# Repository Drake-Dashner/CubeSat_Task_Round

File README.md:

# CubeSat_Task_Round
Contain my Task 3 for CubeSat Task round 1

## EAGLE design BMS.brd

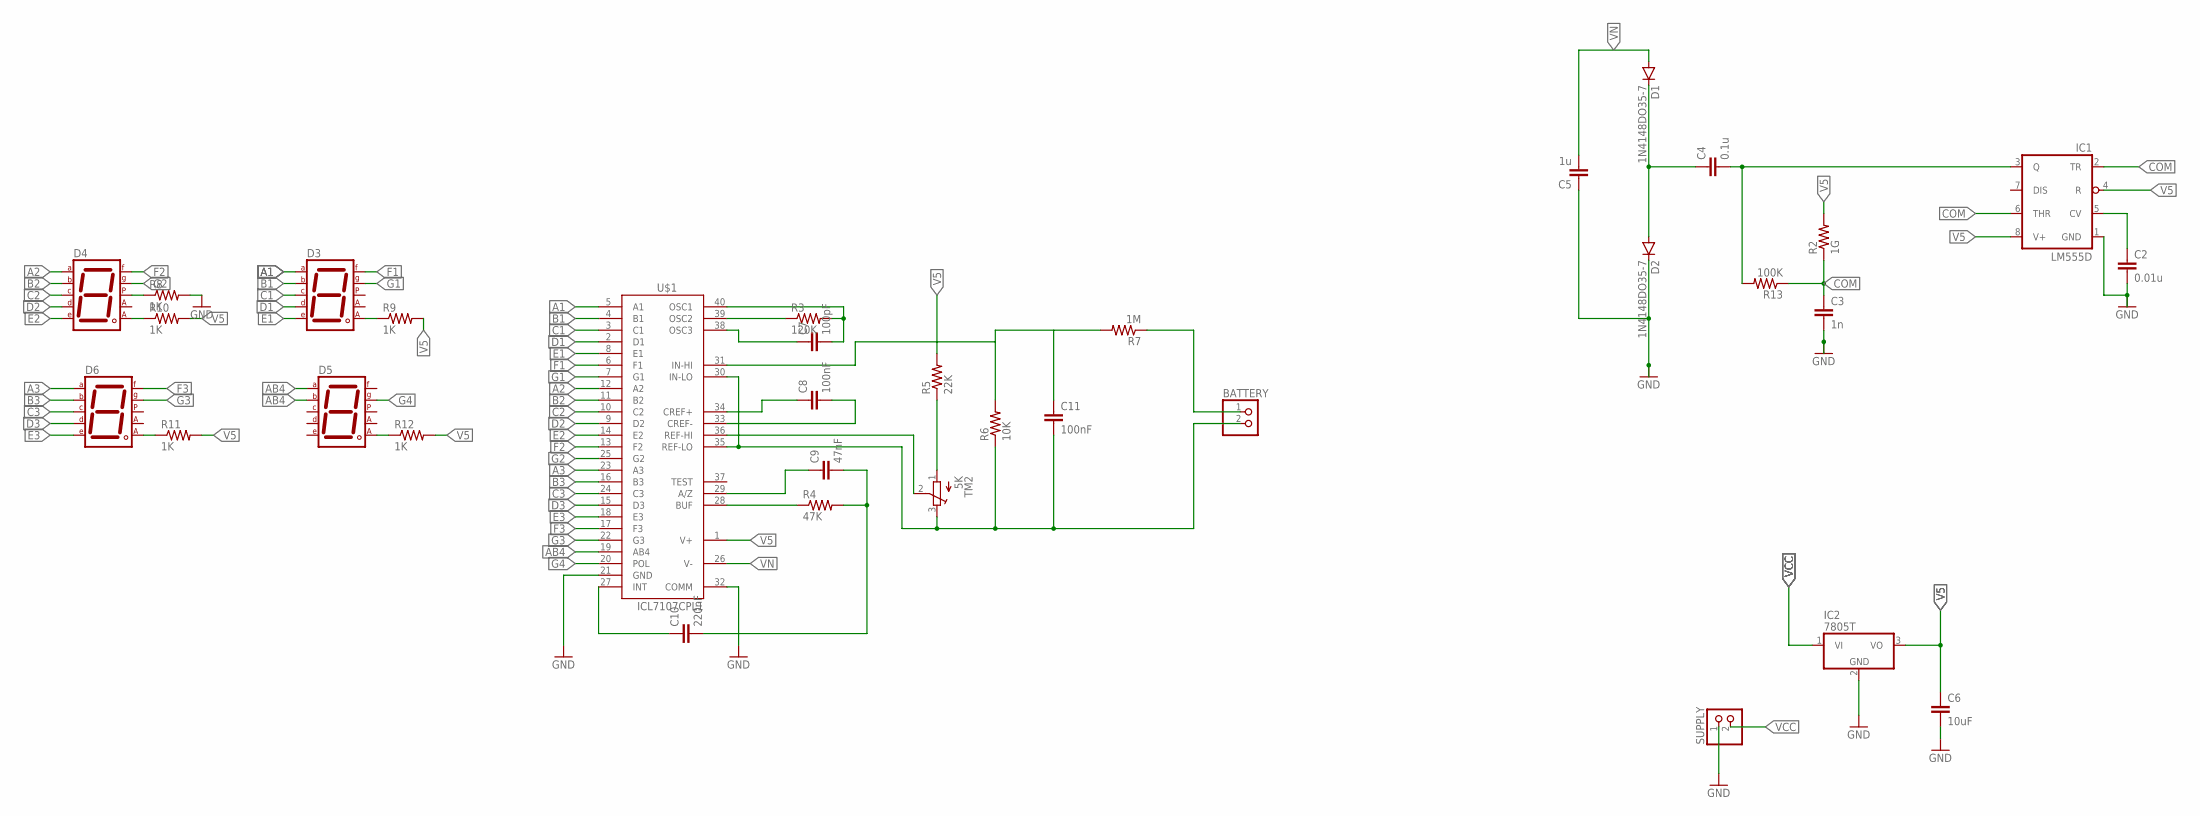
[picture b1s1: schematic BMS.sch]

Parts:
BATTERY: PINHD-1X2; 1X02
C2: 0.01u; C025-025X050
C3: 1n; C025-025X050
C4: 0.1u; C025-025X050
C5: 1u; C025-025X050
C6: 10uF; C025-025X050
C7: 100pF; C025-025X050
C8, C11: 100nF; C025-025X050
C9: 47nF; C025-025X050
C10: 220nF; C025-025X050
D1, D2: 1N4148DO35-7; DO35-7
D3, D4, D5, D6: 7SEG-CA; 7SEG-13
IC1: LM555D; SO08
IC2: 7805T; TO220H
R2: 1G; R0603
R3: 120K; R0603
R4: 47K; R0603
R5: 22K; R0603
R6: 10K; R0603
R7: 1M; R0603
R8, R9, R10, R11, R12: 1K; R0603
R13: 100K; R0603
SUPPLY: PINHD-1X2; 1X02
TM2: 5K; TC33X
U$1: ICL7107CPL1; DIL40

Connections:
A1: D3.7 (A), U$1.5 (A1)
A2: D4.7 (A), U$1.12 (A2)
A3: D6.7 (A), U$1.23 (A3)
AB4: D5.6 (B), D5.7 (A), U$1.19 (AB4)
B1: D3.6 (B), U$1.4 (B1)
B2: D4.6 (B), U$1.11 (B2)
B3: D6.6 (B), U$1.16 (B3)
C1: D3.4 (C), U$1.3 (C1)
C2: D4.4 (C), U$1.10 (C2)
C3: D6.4 (C), U$1.24 (C3)
COM: C3.1, IC1.2 (TR), IC1.6 (THR), R2.1, R13.1
D1: D3.2 (D), U$1.2 (D1)
D2: D4.2 (D), U$1.9 (D2)
D3: D6.2 (D), U$1.15 (D3)
E1: D3.1 (E), U$1.8 (E1)
E2: D4.1 (E), U$1.14 (E2)
E3: D6.1 (E), U$1.18 (E3)
F1: D3.9 (F), U$1.6 (F1)
F2: D4.9 (F), U$1.13 (F2)
F3: D6.9 (F), U$1.17 (F3)
G1: D3.10 (G), U$1.7 (G1)
G2: D4.10 (G), U$1.25 (G2)
G3: D6.10 (G), U$1.22 (G3)
G4: D5.10 (G), U$1.20 (POL)
GND: C2.2, C3.2, C5.1, C6.2, D2.C, IC1.1 (GND), IC2.2 (GND), R8.2, SUPPLY.1, U$1.21 (GND), U$1.32 (COMM)
unnamed: C2.1, IC1.5 (CV)
unnamed: D3.8 (CA2), R9.1
unnamed: C4.2, IC1.3 (Q), R13.2
unnamed: BATTERY.2, C11.2, R6.1, TM2.3 (E), U$1.30 (IN-LO), U$1.35 (REF-LO)
unnamed: C7.2, R3.2, U$1.40 (OSC1)
unnamed: C4.1, D1.C, D2.A
unnamed: R3.1, U$1.39 (OSC2)
unnamed: C7.1, U$1.38 (OSC3)
unnamed: C8.1, U$1.34 (CREF+)
unnamed: C8.2, U$1.33 (CREF-)
unnamed: C9.1, U$1.29 (A/Z)
unnamed: R4.1, U$1.28 (BUF)
unnamed: C9.2, C10.2, R4.2
unnamed: C10.1, U$1.27 (INT)
unnamed: R5.1, TM2.1 (A)
unnamed: R6.2, R7.2, U$1.31 (IN-HI)
unnamed: D4.5 (DP), R8.1
unnamed: BATTERY.1, R7.1
unnamed: TM2.2 (S), U$1.36 (REF-HI)
unnamed: D6.8 (CA2), R11.1
unnamed: D4.8 (CA2), R10.1
unnamed: D5.8 (CA2), R12.1
V5: C6.1, C11.1, IC1.4 (R), IC1.8 (V+), IC2.3 (VO), R2.2, R5.2, R9.2, R10.2, R11.2, R12.2, U$1.1 (V+)
VCC: IC2.1 (VI), SUPPLY.2
VN: C5.2, D1.A, U$1.26 (V-)

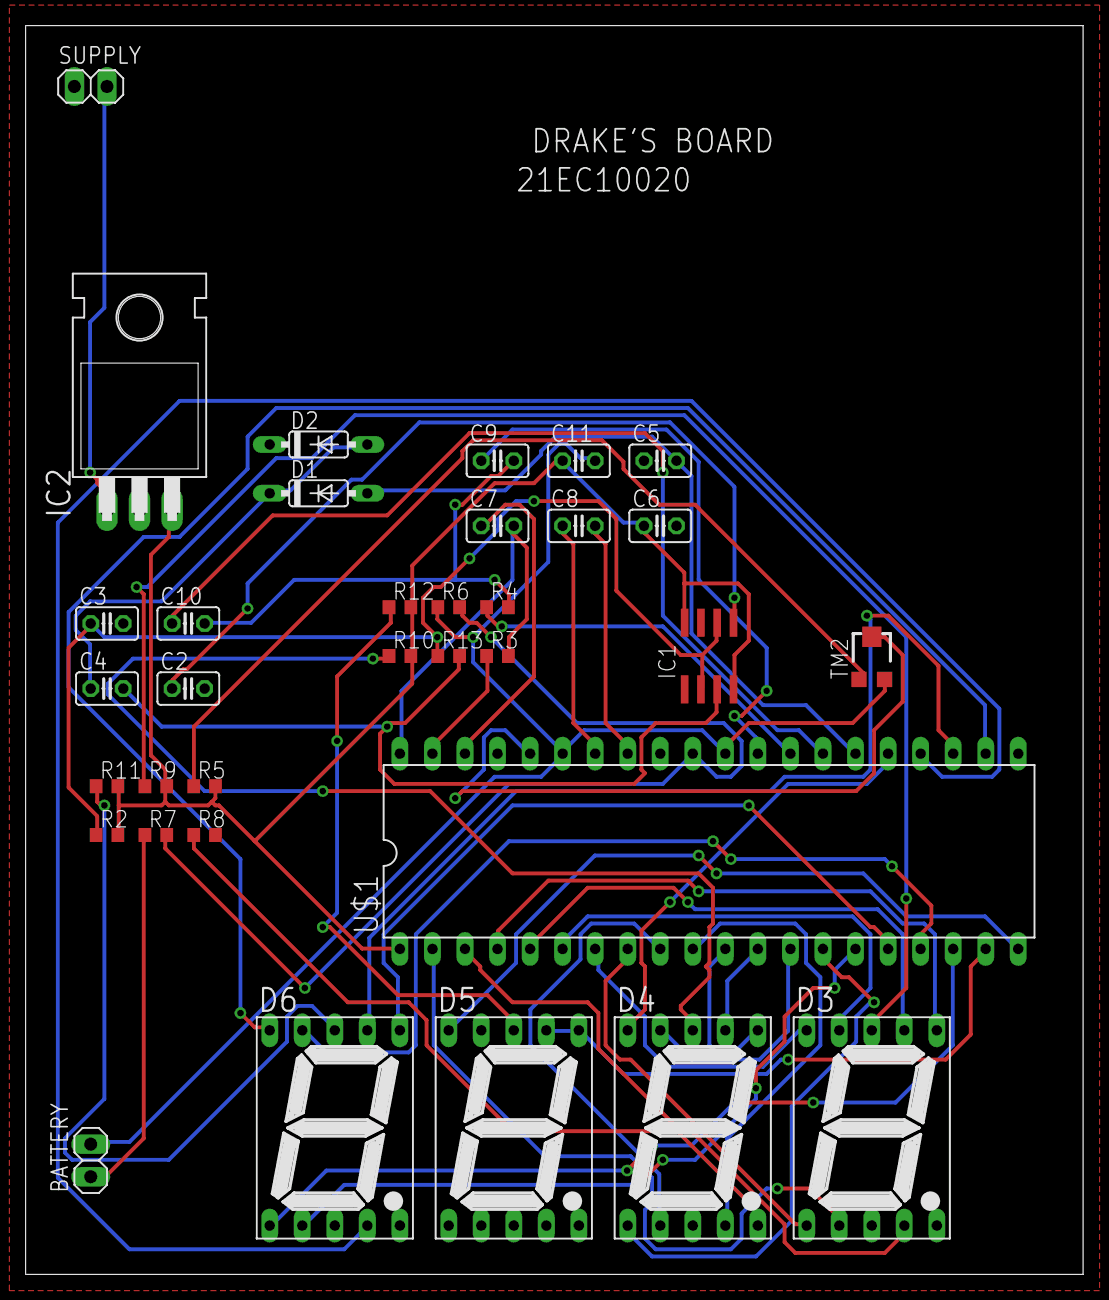
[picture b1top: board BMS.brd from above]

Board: 2 copper layers, 82.5 x 97.5 mm, 34 parts (0 on the bottom side), 50 nets.

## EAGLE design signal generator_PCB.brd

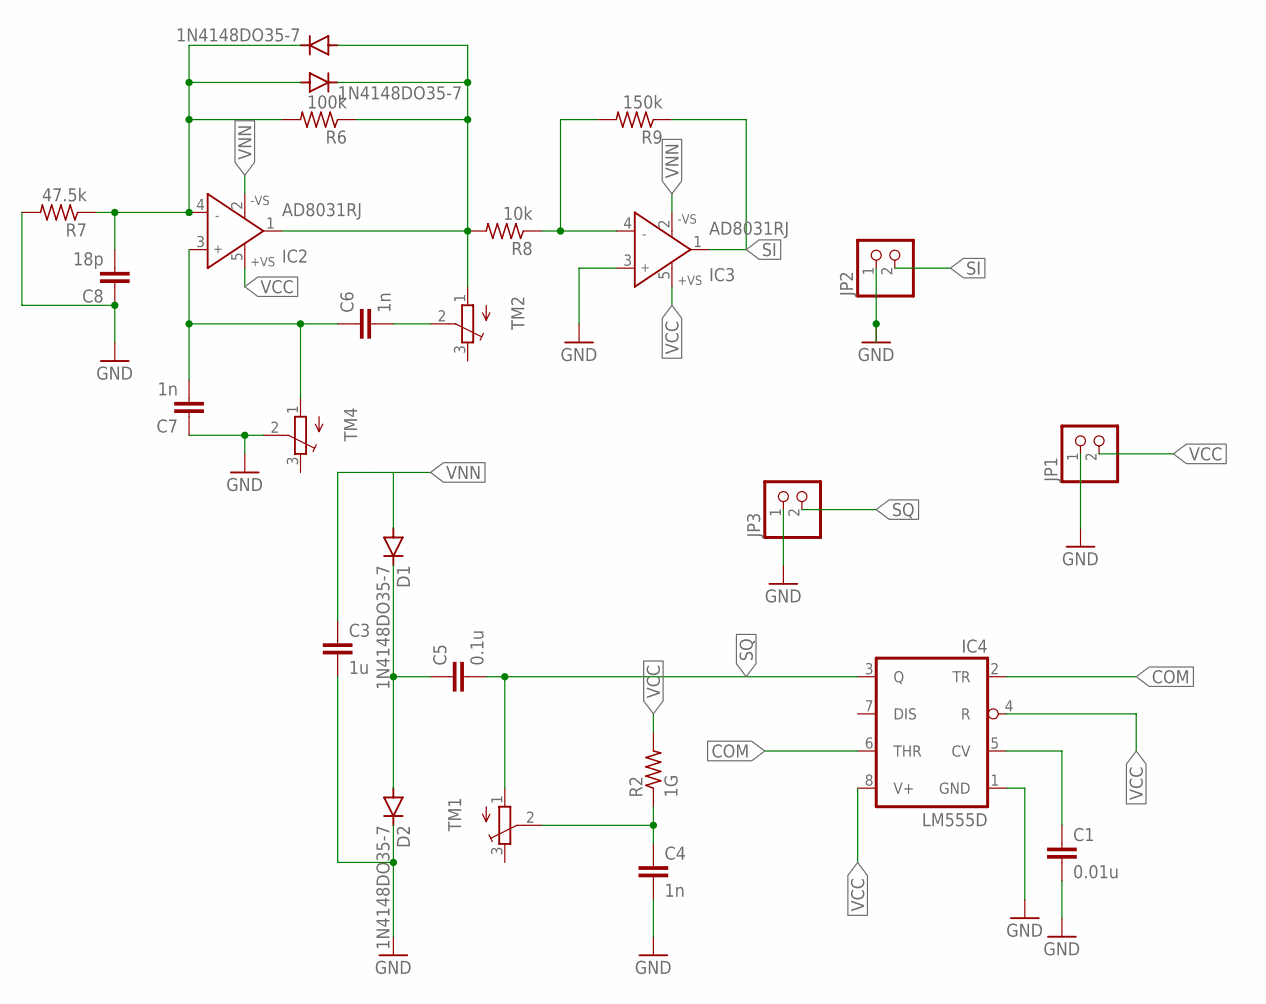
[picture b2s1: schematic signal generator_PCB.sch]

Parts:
C1: 0.01u; C0805
C3: 1u; C0805
C4, C6, C7: 1n; C0805
C5: 0.1u; C0805
C8: 18p; C0805
D1, D2, D3, D4: 1N4148DO35-7; DO35-7
IC2, IC3: AD8031RJ; SOT23-5
IC4: LM555D; SO08
JP1, JP2, JP3: PINHD-1X2; 1X02
R2: 1G; M0805
R6: 100k; M0805
R7: 47.5k; M0805
R8: 10k; M0805
R9: 150k; M0805
TM1, TM2, TM4: TRIMPOTTC33X; TC33X

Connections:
COM: IC4.2 (TR), IC4.6 (THR)
GND: C1.2, C3.2, C4.2, C7.1, C8.1, D2.C, IC3.3 (IN+), IC4.1 (GND), JP1.1, JP2.1, JP3.1, R7.2, TM4.2 (S)
unnamed: C1.1, IC4.5 (CV)
unnamed: C4.1, R2.1, TM1.2 (S)
unnamed: C5.1, D1.C, D2.A
unnamed: C6.2, TM2.2 (S)
unnamed: D3.C, D4.A, IC2.1 (OUT), R6.1, R8.2, TM2.1 (A)
unnamed: C6.1, C7.2, IC2.3 (IN+), TM4.1 (A)
unnamed: C8.2, D3.A, D4.C, IC2.4 (IN-), R6.2, R7.1
unnamed: IC3.4 (IN-), R8.1, R9.2
SI: IC3.1 (OUT), JP2.2, R9.1
SQ: C5.2, IC4.3 (Q), JP3.2, TM1.1 (A)
VCC: IC2.5 (+VS), IC3.5 (+VS), IC4.4 (R), IC4.8 (V+), JP1.2, R2.2
VNN: C3.1, D1.A, IC2.2 (-VS), IC3.2 (-VS)

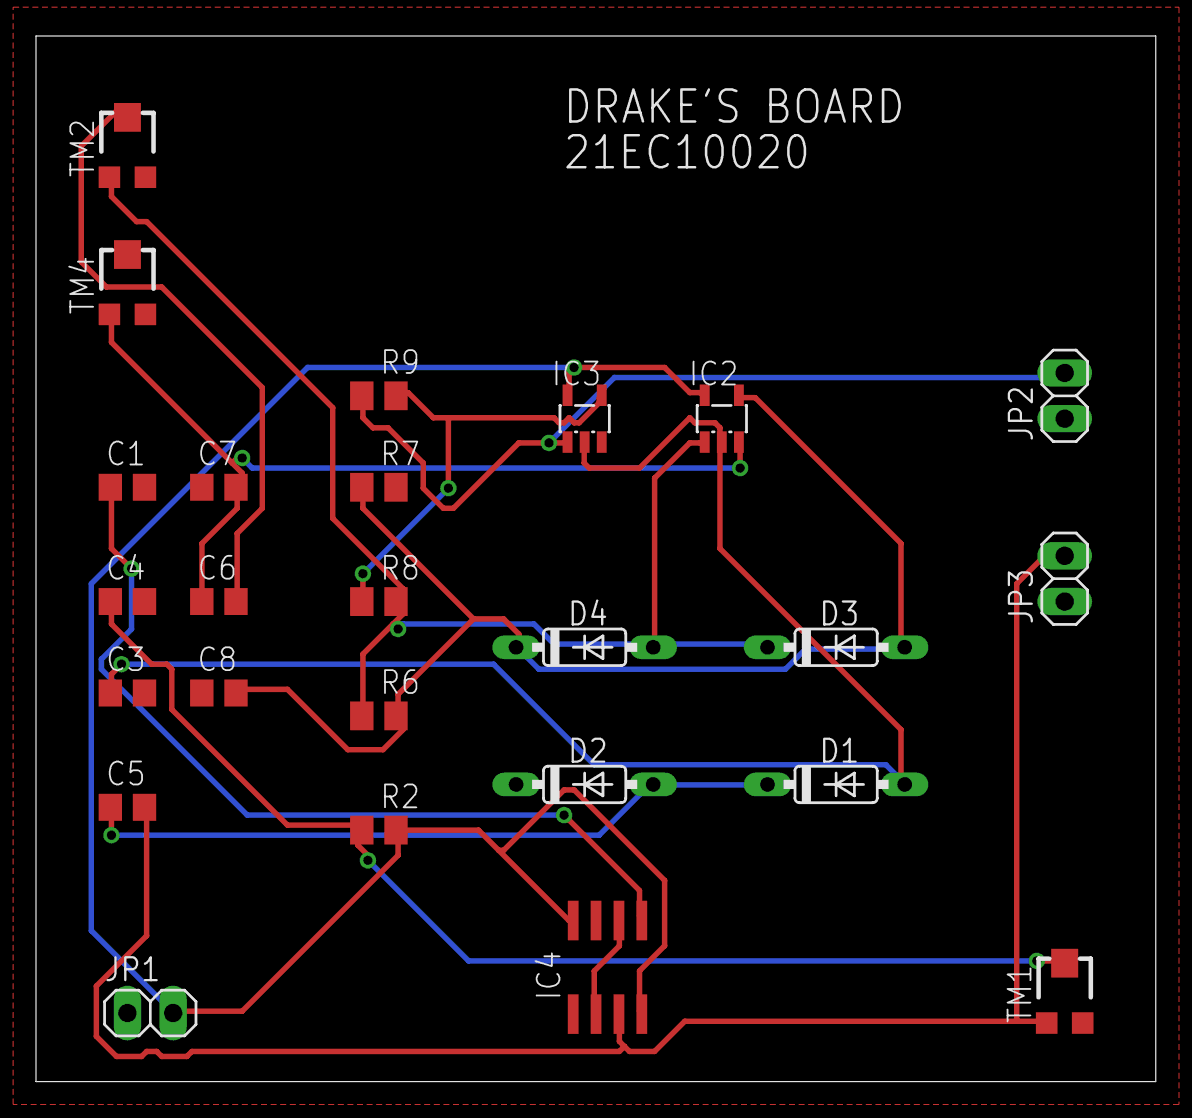
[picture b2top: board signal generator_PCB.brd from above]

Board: 2 copper layers, 62.2 x 58.1 mm, 25 parts (0 on the bottom side), 14 nets.
